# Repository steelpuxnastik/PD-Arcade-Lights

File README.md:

# PD ArcadeLights
Plugin for [PD Loader](https://github.com/PDModdingCommunity/PD-Loader) that sends button LEDs and LEDs on the sides of display (in original arcade cabinet) status to the receiver over UART, that will output this light for you.
As receiver you can use:
1. [Arduino example board](https://github.com/steelpuxnastik/PD-Arcade-Lights/tree/master/PCB) as reference point or as "ready device as is".
2. [PD Arcade picohub](https://github.com/toha-cat/PD_Arcade_picohub) as arcade [controller board](https://github.com/toha-cat/PD_Arcade_picohub/tree/main/PCB) with integrated ArcadeLights possibility.

**I draw your attention to the need to connect the microcontroller board in accordance with the diagram, because the firmware is designed to work with these components. If you understand what and how you want to change this - change it.**

## Features
 - possibility to choose COM-port of your receiver, baudrate and delay of data receiving;
 - possibility to change brightness of partition lights;
 - possibility to ignore partition lights data (partition lights will be turned off, only buttons will work);
 - after closing the game, LEDs automatically turns off;

## Installing
Put `ArcadeLighs.dva` plugin into the `plugins` folder in the PDAFT game folder. Configuration file will be created automatically after you save the settings in **PD Loader**.

## License
  Copyright (c) Project DIVA Modding 2nd Community  
  Copyright (c) [COM14](https://github.com/COM14), [steelpuxnastik](https://github.com/steelpuxnastik), [toha-cat](https://github.com/toha-cat)

  Permission is hereby granted, free of charge, to any person obtaining a copy
  of this software and associated documentation files (the "Software"), to deal
  in the Software without restriction, including without limitation the rights
  to use, copy, modify, merge, publish, distribute, sublicense, and/or sell
  copies of the Software, and to permit persons to whom the Software is
  furnished to do so, subject to the following conditions:
  
  The above copyright notice and this permission notice shall be included in all
  copies or substantial portions of the Software.
  
  THE SOFTWARE IS PROVIDED "AS IS", WITHOUT WARRANTY OF ANY KIND, EXPRESS OR
  IMPLIED, INCLUDING BUT NOT LIMITED TO THE WARRANTIES OF MERCHANTABILITY,
  FITNESS FOR A PARTICULAR PURPOSE AND NONINFRINGEMENT. IN NO EVENT SHALL THE
  AUTHORS OR COPYRIGHT HOLDERS BE LIABLE FOR ANY CLAIM, DAMAGES OR OTHER
  LIABILITY, WHETHER IN AN ACTION OF CONTRACT, TORT OR OTHERWISE, ARISING FROM,
  OUT OF OR IN CONNECTION WITH THE SOFTWARE OR THE USE OR OTHER DEALINGS IN THE
  SOFTWARE.

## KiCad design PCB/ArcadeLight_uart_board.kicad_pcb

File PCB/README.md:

# ArcadeLights PCB example
=================================

## Parts list
- PCB: 1x `ArcadeLight_uart_board` **1.6mm thickness** (KiCad 7.99+ (7.99.0-697-g4d05bd62da), release build required for exporting Gerber files)
  - U1: `Arduino Nano` board
  - U2, U3: 2x `ULN2003` transistor assembly
- Parts for PWM brightness control (short jumpers if no PWM used, **brightness control will not work**):
  - Q1: `IRFR9024N` P-channel MOSFET
  - Q2: `AO3404A` N-channel MOSFET
  - R1: `1k` 1206 SMD resistor
  - R2: `10k` 1206 SMD resistor
- connectors:
  - 2x DIP-16 panel for `ULN2003`
  - 4x `JST XH-02` male connector
  - 3x `JST XH-04` male connector
  - female 2.54 single row headset for `Arduino Nano`

Powering button LEDs in this example setted up from 12v, so you need to be sure that your LEDs can be powered from 12v.
As partition lights you need to use standard **12v RGB LED-strip**. Other types like *5v addressable LED strip* is not sutable and **will not work**.

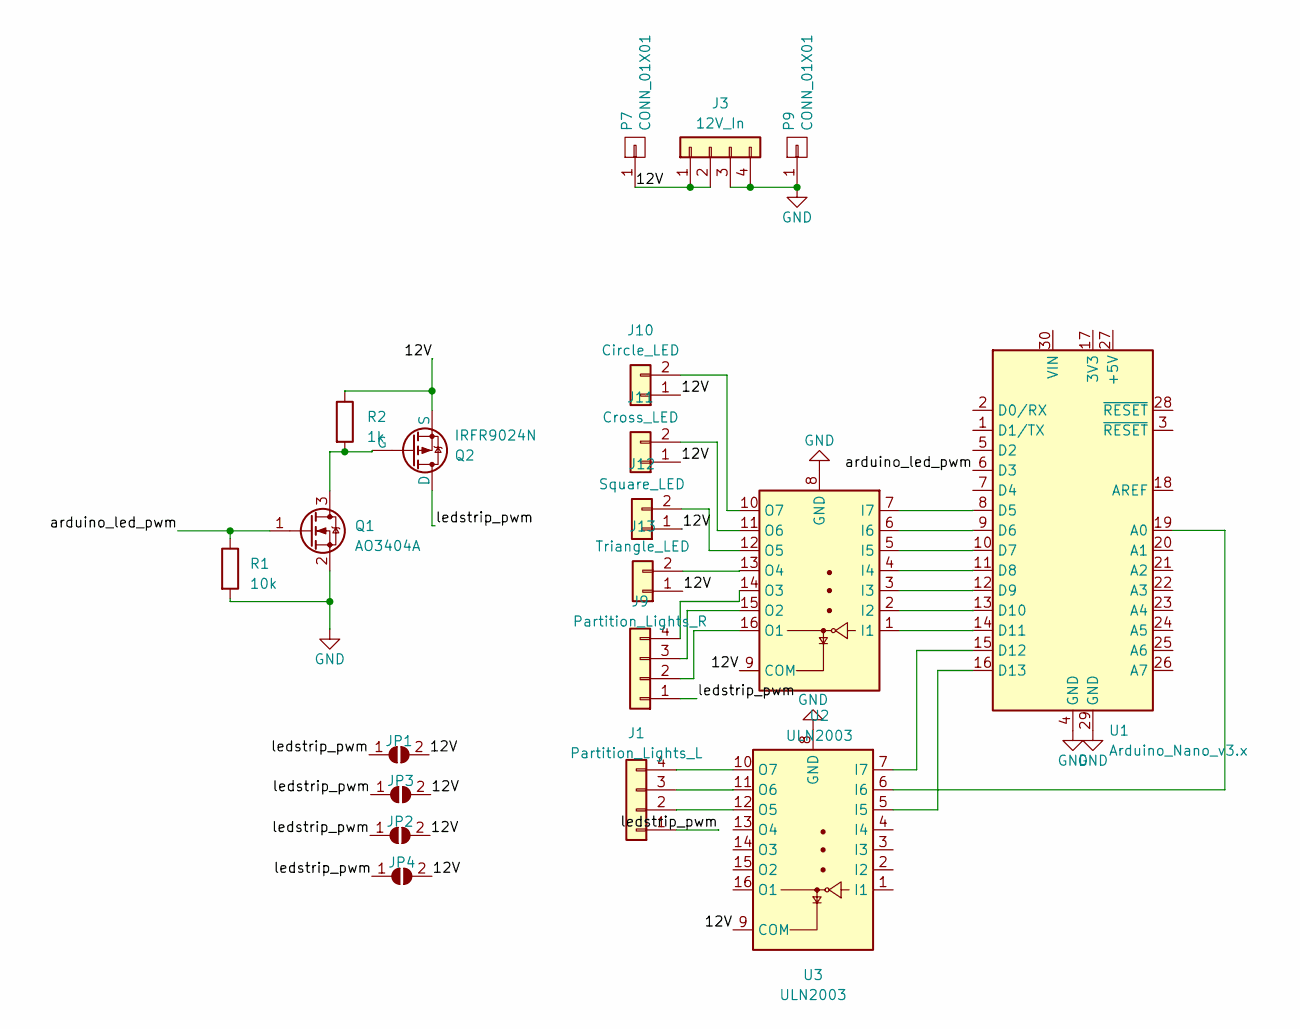
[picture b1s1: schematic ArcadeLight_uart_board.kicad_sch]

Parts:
J1: Partition_Lights_L; JST_XH_B4B-XH-A_1x04_P2.50mm_Vertical
J3: 12V_In; JST_XH_B4B-XH-A_1x04_P2.50mm_Vertical
J9: Partition_Lights_R; JST_XH_B4B-XH-A_1x04_P2.50mm_Vertical
J10: Circle_LED; JST_XH_B2B-XH-A_1x02_P2.50mm_Vertical
J11: Cross_LED; JST_XH_B2B-XH-A_1x02_P2.50mm_Vertical
J12: Square_LED; JST_XH_B2B-XH-A_1x02_P2.50mm_Vertical
J13: Triangle_LED; JST_XH_B2B-XH-A_1x02_P2.50mm_Vertical
JP1, JP2, JP3, JP4: SolderJumper_2_Open; SolderJumper-2_P1.3mm_Open_RoundedPad1.0x1.5mm
P7, P9: CONN_01X01; MountingHole_3.2mm_M3_Pad
Q1: AO3404A; SOT-23
Q2: IRFR9024N; TO-252-2
R1: 10k; R_1206_3216Metric
R2: 1k; R_1206_3216Metric
U1: Arduino_Nano_v3.x; Arduino_Nano
U2, U3: ULN2003; DIP-16_W7.62mm

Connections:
/12V: J3.1, J3.2, J10.1, J11.1, J12.1, J13.1, JP1.2 (B), JP2.2 (B), JP3.2 (B), JP4.2 (B), P7.1, Q2.3 (S), R2.1, U2.9 (COM), U3.9 (COM)
/I1_1: U1.14 (D11), U2.1 (I1)
/I2_1: U1.13 (D10), U2.2 (I2)
/I3_1: U1.12 (D9), U2.3 (I3)
/I4_1: U1.11 (D8), U2.4 (I4)
/I5_1: U1.10 (D7), U2.5 (I5)
/I5_2: U1.16 (D13), U3.5 (I5)
/I6_1: U1.9 (D6), U2.6 (I6)
/I6_2: U1.19 (A0), U3.6 (I6)
/I7_1: U1.8 (D5), U2.7 (I7)
/I7_2: U1.15 (D12), U3.7 (I7)
/arduino_led_pwm: Q1.1 (G), R1.1, U1.6 (D3)
/ledstrip_pwm: J1.1, J9.1, JP1.1 (A), JP2.1 (A), JP3.1 (A), JP4.1 (A), Q2.2 (D)
GND: J3.3, J3.4, P9.1, Q1.2 (S), R1.2, U1.4 (GND), U1.29 (GND), U2.8 (GND), U3.8 (GND)
unnamed: J1.2, U3.12 (O5)
unnamed: J1.3, U3.11 (O6)
unnamed: J1.4, U3.10 (O7)
unnamed: J9.2, U2.16 (O1)
unnamed: J9.3, U2.15 (O2)
unnamed: J9.4, U2.14 (O3)
unnamed: J10.2, U2.10 (O7)
unnamed: J11.2, U2.11 (O6)
unnamed: J12.2, U2.12 (O5)
unnamed: J13.2, U2.13 (O4)
unnamed: Q1.3 (D), Q2.1 (G), R2.2

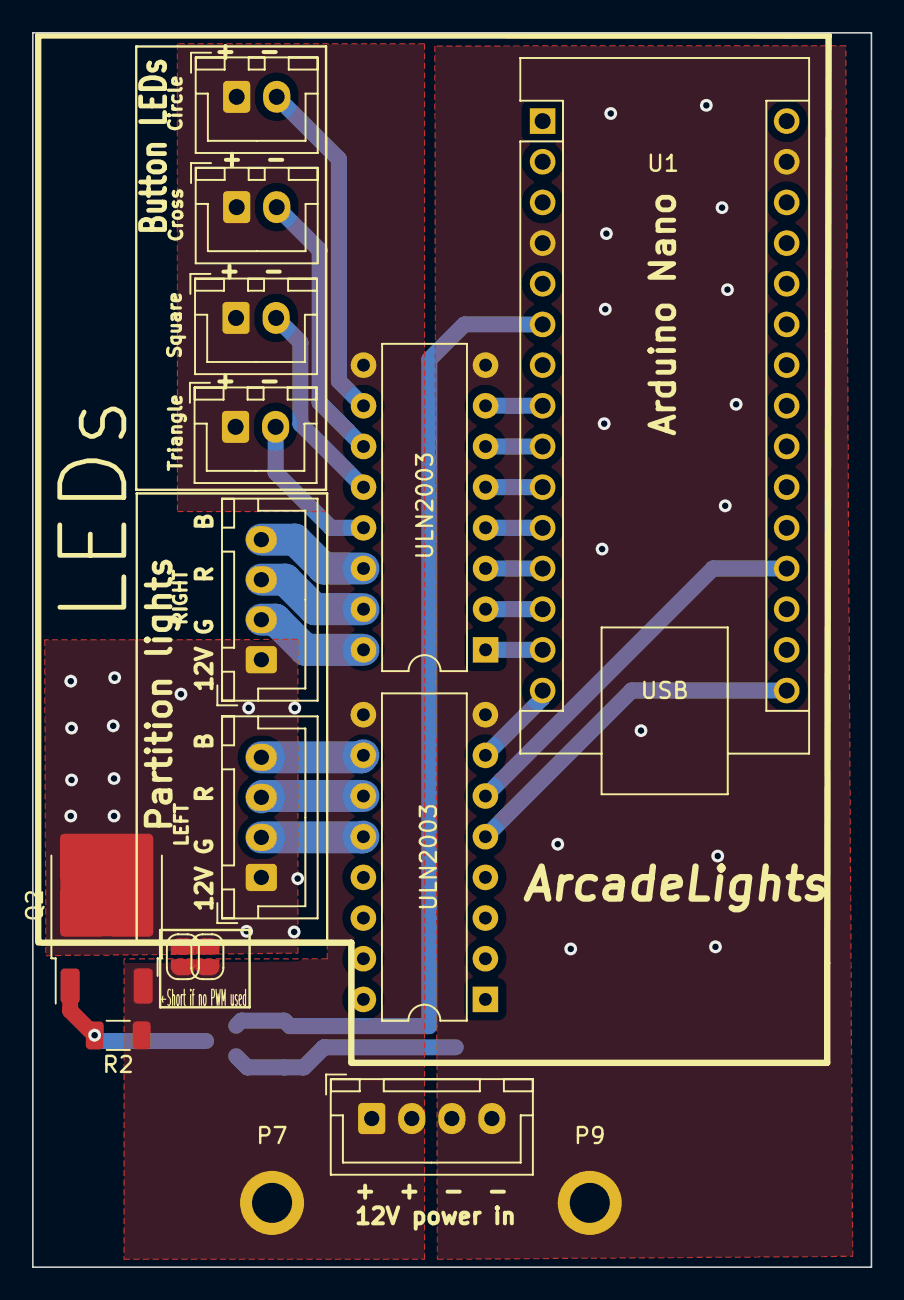
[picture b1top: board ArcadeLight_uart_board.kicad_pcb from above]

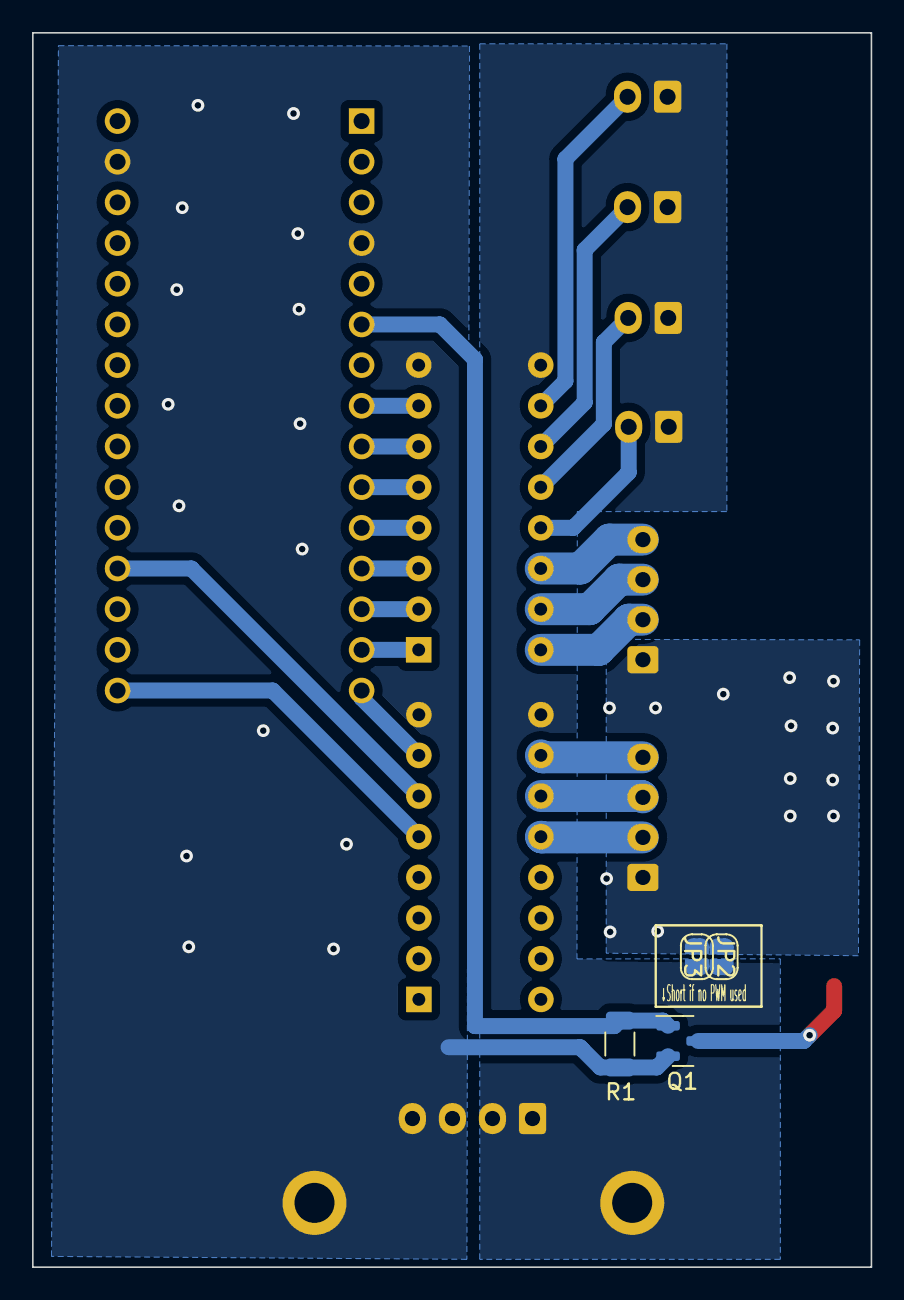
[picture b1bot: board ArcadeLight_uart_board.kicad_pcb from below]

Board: 2 copper layers, 52.4 x 77.1 mm, 20 parts (4 on the bottom side), 24 nets.

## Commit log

2024-09-26 vs19 Solution
2024-09-26 plugin crash fix, port change, lights turns off after game close
    Critial error that plugin didn't work after crash or mistake connection - fixed, fixed possibility to change port and lights turns off after closing the game. To do: fix option captions in plugin
2024-09-27 Plugin settings edit
    Added description to plugin settings for what it's used and help button with link to github
2024-09-27 targetname change
    to ArcadeLights
2024-09-27 added settings file check
    creation settings file if it's not present
2024-09-27 Added plugin description
2024-09-27 Update of transfer algorithm
    Data sends to receiver only if changes detected
2024-09-27 Update of Arduino FW due to changes in plugin
2024-09-27 fix of turning off lights when closing the game
2024-09-30 Turns on all LEDs when connection established
    Found problem that sometimes LEDs not turns on when connection established. Now forcibly sends signal to turn on all LEDs but even this not always helps, so you need press F1 to go to service menu an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
2024-10-07 praparing to add ignore of partition lights ouput
2024-10-11 exclusive display mode somehow works now and ignoring of partition lights too
2024-11-05 fixing connection problem to PD_Arcade_picohub
2024-11-07 added PWM control or partition lights brightness and example of PCB that can be used
2024-11-08 Arduino program PWM brightness control added
2024-11-25 R1 fix to 1k
    10k do not work
2025-01-07 Readme update
